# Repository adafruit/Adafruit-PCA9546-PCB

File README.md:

## Adafruit PCA9546 4-Channel I2C Multiplexer PCB

<a href="http://www.adafruit.com/products/5663"><br/>
Click here to purchase one from the Adafruit shop</a>
<br>
<a href="http://www.adafruit.com/products/5664"><br/>
Click here to purchase one from the Adafruit shop</a>

PCB files for the Adafruit PCA9546 4-Channel I2C Multiplexer and STEMMA QT / Qwiic PCA9546 Breakout. 

Format is EagleCAD schematic and board layout
* https://www.adafruit.com/product/5663
* https://www.adafruit.com/product/5664

### Description

You just found the perfect I2C sensor, and you want to wire up two or three or more of them to your Arduino when you realize "Uh oh, this chip has a fixed I2C address, and from what I know about I2C, you cannot have two devices with the same address on the same SDA/SCL pins!" Are you out of luck? You would be if you didn't have this ultra-cool PCA9546 1-to-4 I2C multiplexer!

Finally, a way to get up to 4 same-address I2C devices hooked up to one microcontroller - this multiplexer acts as a gatekeeper, shuttling the commands to the selected set of I2C pins with your command.  If you need to have up to 8 multiplexed devices, check out the 8-channel TCA9548 version of this board.

Using it is fairly straight-forward: the multiplexer itself is on I2C address 0x70 (but can be adjusted from 0x70 to 0x77) and you simply write a single byte with the desired multiplexed output number to that port, and bam - any future I2C packets will get sent to that port. In theory, you could have 8 of these multiplexers on each of 0x70-0x77 addresses in order to control 8*4 = 32 of the same-I2C-addressed-part.

Like all Adafruit breakouts, we put this nice chip on a breakout for you so you can use it on a breadboard with capacitors, and pullups and pulldowns to make usage a snap. Some header is required, and once soldered, you can plug it into a solderless breadboard. The chip itself is 3V and 5V compliant, so you can use it with any logic level.

Comes with only the assembled PCB, no cables or sensors included (we have tons available though!)

The Adafruit STEMMA QT / Qwiic PCA9546 Breakout - 4 Channel has five JST SH 1mm connectors: 1 input and 4 outputs. There's one port at the end that connects to your I2C controller (there are also breadboard breakout pins if you need them). Use this breakout to add as many I2C devices to the bus as you need. Complete with mounting holes so the board can be added to any system. A small power LED lets you know that the hub board has connectivity.

There's even an onboard 3.3V 500mA regulator, so if you're using this with a 5V microcontroller like an Arduino 328-compatible, you can level shift all the QT ports to have 3V power and logic level. Simply cut/solder the jumper on the bottom of the PCB to change the power and logic level to be forced 3V.

### License

Adafruit invests time and resources providing this open source design, please support Adafruit and open-source hardware by purchasing products from [Adafruit](https://www.adafruit.com)!

Designed by Limor Fried/Ladyada for Adafruit Industries.

Creative Commons Attribution/Share-Alike, all text above must be included in any redistribution. 
See license.txt for additional details.

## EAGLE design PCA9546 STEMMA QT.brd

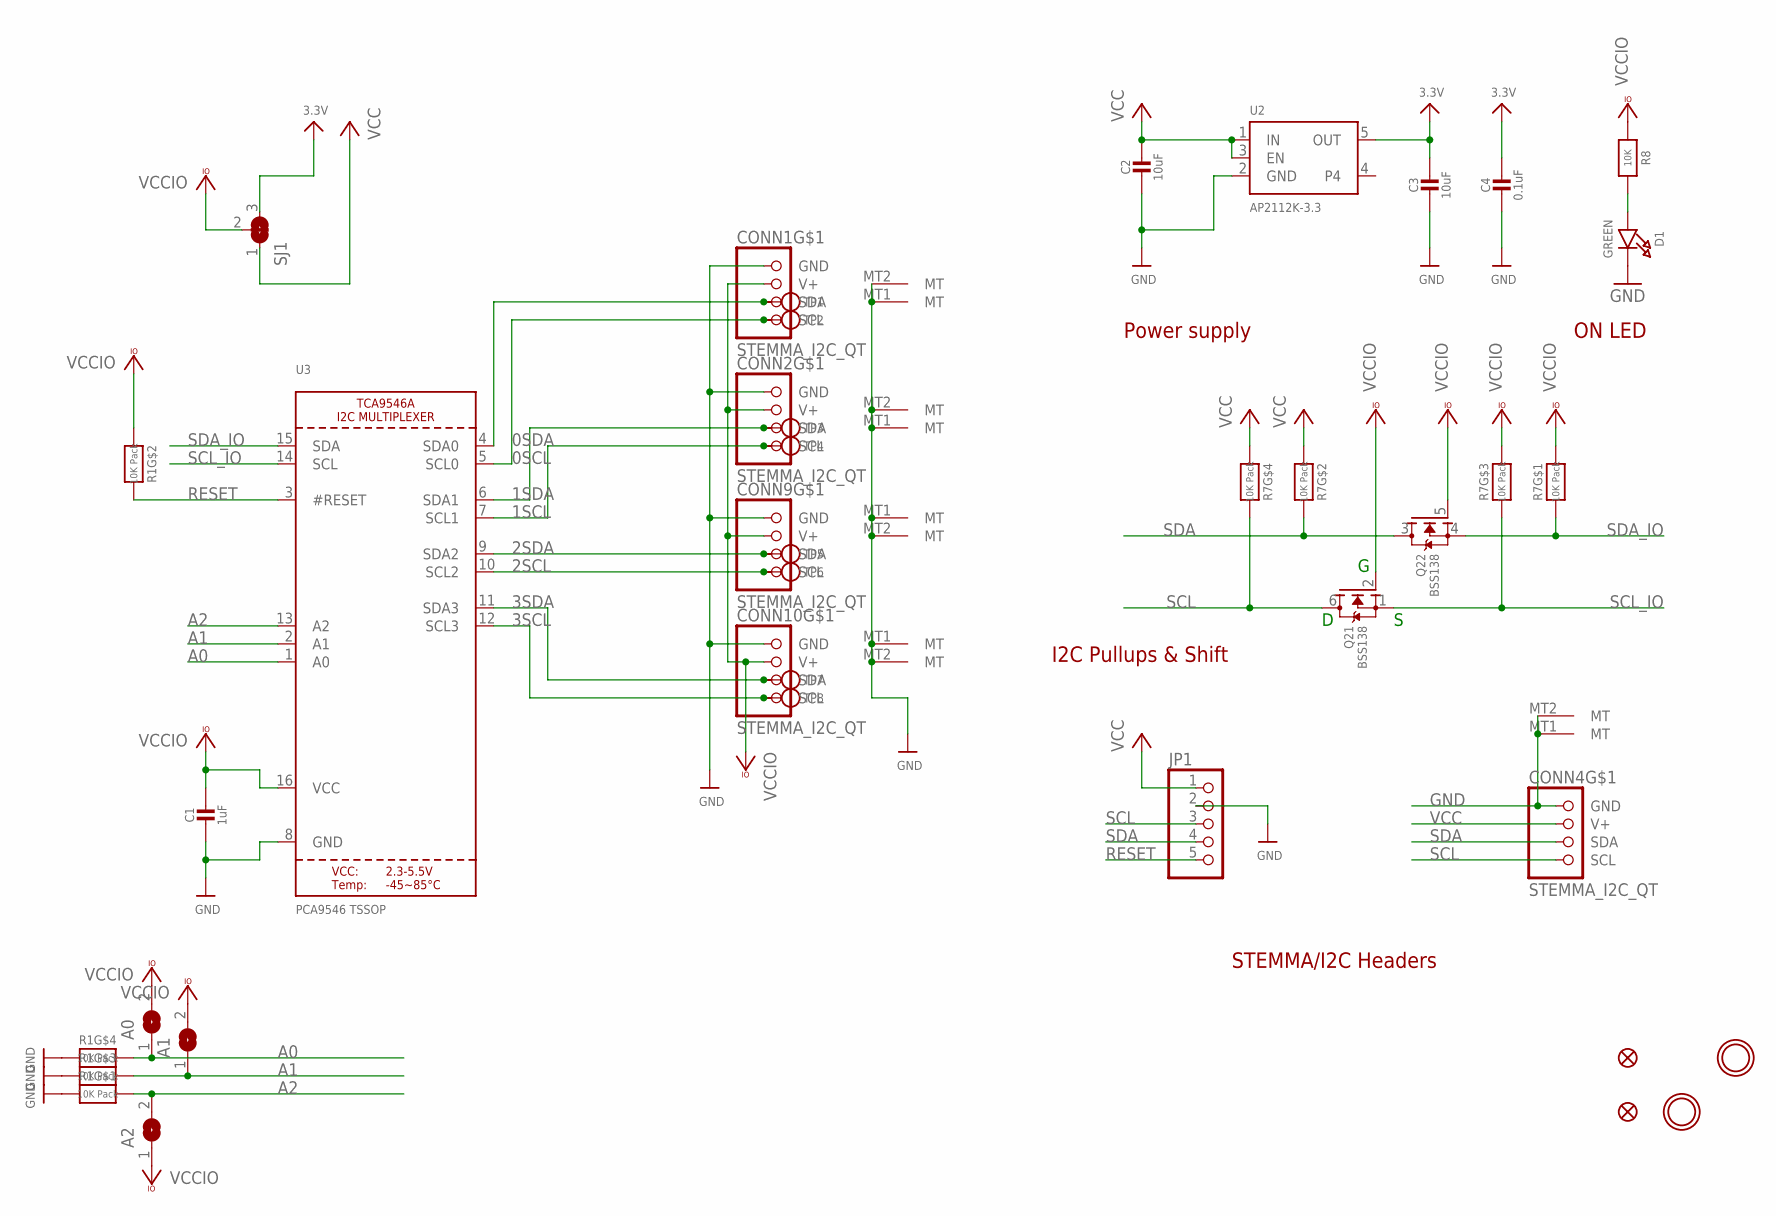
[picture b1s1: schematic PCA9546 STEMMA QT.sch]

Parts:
A0, A1, A2: SOLDERJUMPER; SOLDERJUMPER_ARROW_NOPASTE
C1: 1uF; 0603-NO
C2, C3: 10uF; 0805-NO
C4: 0.1uF; 0603-NO
CONN1, CONN2, CONN4, CONN9, CONN10: STEMMA_I2C_QT; JST_SH4
D1: GREEN; CHIPLED_0603_NOOUTLINE
FID2, FID4: FIDUCIAL_1MM
JP1: HEADER-1X570MIL; 1X05_ROUND_70
Q2: BSS138; SOT363
R1, R7: 10K Pack; RESPACK_4X0603
R8: 10K; 0603-NO
SJ1: SOLDERJUMPER_2WAY; SOLDERJUMPER_2WAY_OPEN_NOPASTE
TP1, TP2, TP3, TP4, TP5, TP6, TP7, TP8: TESTPOINTROUND1.5MMNO; TESTPOINT_ROUND_1.5MM_NO
U2: AP2112K-3.3; SOT23-5; JLC_ROTATION 0
U3: PCA9546 TSSOP; TSSOP16
U$19, U$22: MOUNTINGHOLE2.5; MOUNTINGHOLE_2.5_PLATED

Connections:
0SCL: CONN1.4 (SCL), TP2.P$1, U3.5 (SCL0)
0SDA: CONN1.3 (SDA), TP1.P$1, U3.4 (SDA0)
1SCL: CONN2.4 (SCL), TP4.P$1, U3.7 (SCL1)
1SDA: CONN2.3 (SDA), TP3.P$1, U3.6 (SDA1)
2SCL: CONN9.4 (SCL), TP6.P$1, U3.10 (SCL2)
2SDA: CONN9.3 (SDA), TP5.P$1, U3.9 (SDA2)
3.3V: C3.1, C4.1, SJ1.3, U2.5 (OUT)
3SCL: CONN10.4 (SCL), TP8.P$1, U3.12 (SCL3)
3SDA: CONN10.3 (SDA), TP7.P$1, U3.11 (SDA3)
A0: A0.1, R1.5 (2), U3.1 (A0)
A1: A1.1, R1.6 (2), U3.2 (A1)
A2: A2.2, R1.8 (2), U3.13 (A2)
GND: C1.2, C2.2, C3.2, C4.2, CONN1.1 (GND), CONN1.MT1 (MT), CONN1.MT2 (MT), CONN2.1 (GND), CONN2.MT1 (MT), CONN2.MT2 (MT), CONN4.1 (GND), CONN4.MT1 (MT), CONN4.MT2 (MT), CONN9.1 (GND), CONN9.MT1 (MT), CONN9.MT2 (MT), CONN10.1 (GND), CONN10.MT1 (MT), CONN10.MT2 (MT), D1.C, JP1.2, R1.1, R1.3 (1), R1.4 (1), U2.2 (GND), U3.8 (GND)
unnamed: D1.A, R8.2
RESET: JP1.5, R1.7 (2), U3.3 (#RESET)
SCL: CONN4.4 (SCL), JP1.3, Q2.6 (D), R7.5 (2)
SCL_IO: Q2.1 (S), R7.6 (2), U3.14 (SCL)
SDA: CONN4.3 (SDA), JP1.4, Q2.3 (D), R7.7 (2)
SDA_IO: Q2.4 (S), R7.8 (2), U3.15 (SDA)
VCC: C2.1, CONN4.2 (V+), JP1.1, R7.2 (1), R7.4 (1), SJ1.1, U2.1 (IN), U2.3 (EN)
VCCIO: A0.2, A1.2, A2.1, C1.1, CONN1.2 (V+), CONN2.2 (V+), CONN9.2 (V+), CONN10.2 (V+), Q2.2 (G), Q2.5 (G), R1.2 (1), R7.1, R7.3 (1), R8.1, SJ1.2, U3.16 (VCC)

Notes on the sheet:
I2C Pullups & Shift
STEMMA/I2C Headers
ON LED
Power supply

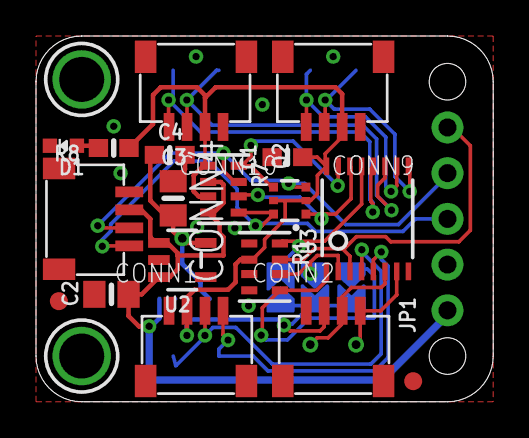
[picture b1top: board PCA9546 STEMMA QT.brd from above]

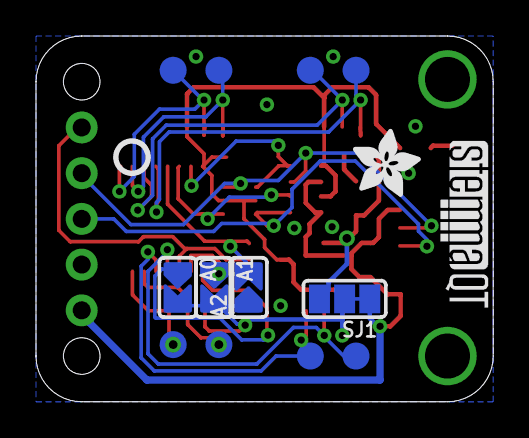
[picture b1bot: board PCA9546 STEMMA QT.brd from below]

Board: 2 copper layers, 25.4 x 20.3 mm, 55 parts (24 on the bottom side), 21 nets.

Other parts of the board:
PLABEL0: PLABEL0
PLABEL1: PLABEL1
PLABEL2: PLABEL2
PLABEL3: PLABEL3
PLABEL4: PLABEL4
PLABEL5: PLABEL5
PLABEL6: PLABEL6
PLABEL7: PLABEL7
PLABEL8: PLABEL8
PLABEL9: PLABEL9
PLABEL10: PLABEL10
PLABEL11: PLABEL11
PLABEL12: PLABEL12
PLABEL13: PLABEL13
PLABEL14: PLABEL14
PLABEL15: PLABEL15
PLABEL16: PLABEL16
PLABEL17: PLABEL17
PLABEL18: PLABEL18
U$28: ADAFRUIT_3.5MM
U$29: PCBFEAT-REV-040
U$31: STEMMAQT

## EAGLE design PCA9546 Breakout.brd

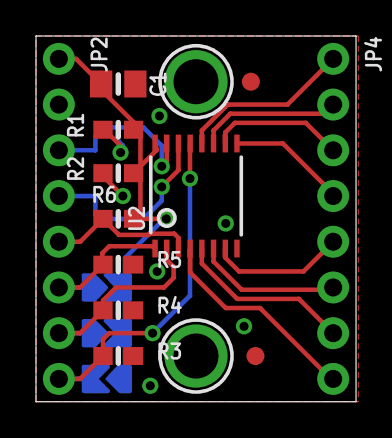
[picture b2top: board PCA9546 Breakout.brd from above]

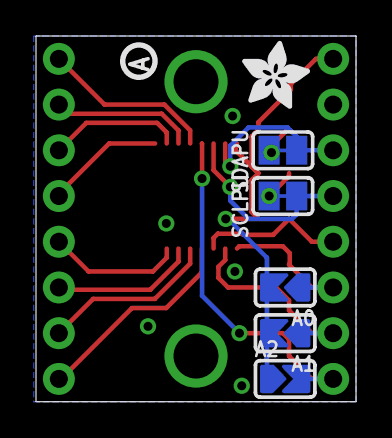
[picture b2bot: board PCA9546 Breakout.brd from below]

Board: 2 copper layers, 17.8 x 20.3 mm, 44 parts (13 on the bottom side), 18 nets.

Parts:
A0, A1, A2: SOLDERJUMPER_ARROW_NOPASTE
C1: 10uF; 0805-NO
FID1, FID3: FIDUCIAL_1MM
JP2, JP4: 1X08_ROUND_70
PLABEL0: PLABEL0
PLABEL1: PLABEL1
PLABEL2: PLABEL2
PLABEL3: PLABEL3
PLABEL4: PLABEL4
PLABEL5: PLABEL5
PLABEL6: PLABEL6
PLABEL7: PLABEL7
PLABEL8: PLABEL8
PLABEL9: PLABEL9
PLABEL10: PLABEL10
PLABEL11: PLABEL11
PLABEL12: PLABEL12
PLABEL13: PLABEL13
PLABEL14: PLABEL14
PLABEL15: PLABEL15
PLABEL16: PLABEL16
PLABEL17: PLABEL17
PLABEL18: PLABEL18
PLABEL19: PLABEL19
PLABEL20: PLABEL20
PLABEL21: PLABEL21
PLABEL22: PLABEL22
R1, R2, R3, R4, R5, R6: 10K; 0603-NO
SCLPU: SOLDERJUMPER_CLOSEDWIRE
SDAPU: SOLDERJUMPER_CLOSEDWIRE
U2: PCA9546A TSSOP; TSSOP16
U$4, U$5: MOUNTINGHOLE2.5; MOUNTINGHOLE_2.5_PLATED
U$6: PCBFEAT-REV-040
U$7: ADAFRUIT_3.5MM

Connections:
0SCL: JP4.7, U2.5
0SDA: JP4.8, U2.4
1SCL: JP4.5, U2.7
1SDA: JP4.6, U2.6
2SCL: JP4.3, U2.10
2SDA: JP4.4, U2.9
3SCL: JP4.1, U2.12
3SDA: JP4.2, U2.11
A0: A0.1, JP2.6, R5.1, U2.1
A1: A1.1, JP2.7, R4.1, U2.2
A2: A2.2, JP2.8, R3.1, U2.13
GND: C1.2, JP2.2, R3.2, R4.2, R5.2, U2.8
INPUTSCL: JP2.4, SCLPU.1, U2.14
INPUTSDA: JP2.3, SDAPU.1, U2.15
unnamed: R2.1, SCLPU.2
unnamed: R1.1, SDAPU.2
RESET: JP2.5, R6.1, U2.3
VCC: A0.2, A1.2, A2.1, C1.1, JP2.1, R1.2, R2.2, R6.2, U2.16

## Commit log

2023-01-10 adding cookiecutter output
2023-01-10 updating readme
2024-06-25 new silk
2024-06-25 remove extra eagle

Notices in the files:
parts and their libraries:
microbuilder: This work is placed in the public domain, and may be freely used for commercial and non-commercial work with the following conditions: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
